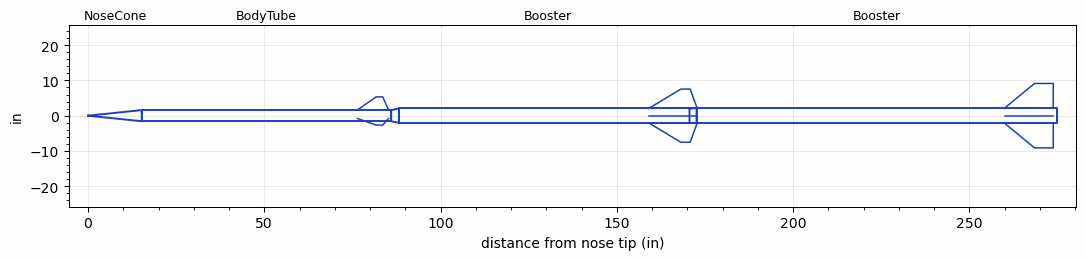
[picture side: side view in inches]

<RASAeroDocument>
 <FileVersion>2</FileVersion>
 <RocketDesign>
  <NoseCone>
   <Length>15.25</Length>
   <Diameter>3.17</Diameter>
   <Shape>Conical</Shape>
   <Location>0</Location>
  </NoseCone>
  <BodyTube>
   <Length>70.75</Length>
   <Diameter>3.17</Diameter>
   <Location>15.25</Location>
   <Fin>
    <Count>3</Count>
    <Chord>8.875</Chord>
    <Span>3.75</Span>
    <SweepDistance>5.3564</SweepDistance>
    <TipChord>1.875</TipChord>
    <Thickness>0.188</Thickness>
    <Location>9.625</Location>
    <AirfoilSection>Hexagonal</AirfoilSection>
    <FX1>0.75</FX1>
    <FX3>0.75</FX3>
   </Fin>
  </BodyTube>
  <Booster>
   <Length>84.625</Length>
   <Diameter>4.1</Diameter>
   <InsideDiameter>3.17</InsideDiameter>
   <Location>86</Location>
   <ShoulderLength>2.1875</ShoulderLength>
   <Fin>
    <Count>4</Count>
    <Chord>13.75</Chord>
    <Span>5.5</Span>
    <SweepDistance>9.125</SweepDistance>
    <TipChord>2.625</TipChord>
    <Thickness>0.23</Thickness>
    <Location>13.75</Location>
    <AirfoilSection>Hexagonal</AirfoilSection>
    <FX1>1</FX1>
    <FX3>1</FX3>
   </Fin>
  </Booster>
  <Booster>
   <Length>102.1875</Length>
   <Diameter>4.28</Diameter>
   <InsideDiameter>4.1</InsideDiameter>
   <LaunchShoeArea>0.233</LaunchShoeArea>
   <Location>170.625</Location>
   <ShoulderLength>2</ShoulderLength>
   <Fin>
    <Count>4</Count>
    <Chord>13.8125</Chord>
    <Span>7</Span>
    <SweepDistance>8.5</SweepDistance>
    <TipChord>5.3125</TipChord>
    <Thickness>0.32</Thickness>
    <Location>14.8125</Location>
    <AirfoilSection>Hexagonal Blunt Base</AirfoilSection>
    <FX1>1</FX1>
   </Fin>
  </Booster>
  <Surface>Smooth Paint</Surface>
  <ModifiedBarrowman>True</ModifiedBarrowman>
  <Turbulence>True</Turbulence>
  <UseBooster1>False</UseBooster1>
  <UseBooster2>False</UseBooster2>
 </RocketDesign>
 <LaunchSite>
  <Altitude>3750</Altitude>
  <Pressure>0</Pressure>
  <RodAngle>0</RodAngle>
  <RodLength>18</RodLength>
  <Temperature>80</Temperature>
  <WindSpeed>0</WindSpeed>
 </LaunchSite>
 <Recovery>
  <Altitude1>1000</Altitude1>
  <Altitude2>1000</Altitude2>
  <DeviceType1>None</DeviceType1>
  <DeviceType2>None</DeviceType2>
  <Event1>False</Event1>
  <Event2>False</Event2>
  <Size1>1</Size1>
  <Size2>1</Size2>
  <EventType1>None</EventType1>
  <EventType2>None</EventType2>
  <CD1>1.33</CD1>
  <CD2>1.33</CD2>
 </Recovery>
 <SimulationList>
  <Simulation>
   <SustainerEngine>M745WC  (GM)</SustainerEngine>
   <SustainerLaunchWt>21.6</SustainerLaunchWt>
   <SustainerNozzleDiameter>1</SustainerNozzleDiameter>
   <SustainerCG>56</SustainerCG>
   <SustainerIgnitionDelay>20.6</SustainerIgnitionDelay>
   <Booster1Engine>N2501-WH-P  (CTI)</Booster1Engine>
   <Booster1LaunchWt>67.63</Booster1LaunchWt>
   <Booster1SeparationDelay>0.9</Booster1SeparationDelay>
   <Booster1IgnitionDelay>6.5</Booster1IgnitionDelay>
   <Booster1CG>116</Booster1CG>
   <Booster1NozzleDiameter>1.75</Booster1NozzleDiameter>
   <IncludeBooster1>True</IncludeBooster1>
   <Booster2Engine>N5800-CS  (CTI)</Booster2Engine>
   <Booster2LaunchWt>122.8</Booster2LaunchWt>
   <Booster2Delay>0.9</Booster2Delay>
   <Booster2CG>177</Booster2CG>
   <Booster2NozzleDiameter>2.5</Booster2NozzleDiameter>
   <IncludeBooster2>True</IncludeBooster2>
   <TimetoApogee>121.5339</TimetoApogee>
   <MaxAltitude>155381.8</MaxAltitude>
   <MaxVelocity>2656.705</MaxVelocity>
  </Simulation>
  <Simulation>
   <SustainerEngine>M1401  (Ces)</SustainerEngine>
   <SustainerLaunchWt>23.6</SustainerLaunchWt>
   <SustainerNozzleDiameter>1</SustainerNozzleDiameter>
   <SustainerCG>60.2</SustainerCG>
   <SustainerIgnitionDelay>7.4</SustainerIgnitionDelay>
   <Booster1Engine>N1560-WH-MB-P  (CTI)</Booster1Engine>
   <Booster1LaunchWt>76.5</Booster1LaunchWt>
   <Booster1SeparationDelay>5</Booster1SeparationDelay>
   <Booster1IgnitionDelay>8.1</Booster1IgnitionDelay>
   <Booster1CG>118.6</Booster1CG>
   <Booster1NozzleDiameter>2.5</Booster1NozzleDiameter>
   <IncludeBooster1>True</IncludeBooster1>
   <Booster2Engine>N5800-CS  (CTI)</Booster2Engine>
   <Booster2LaunchWt>131.9</Booster2LaunchWt>
   <Booster2Delay>1</Booster2Delay>
   <Booster2CG>168.6</Booster2CG>
   <Booster2NozzleDiameter>2.5</Booster2NozzleDiameter>
   <IncludeBooster2>True</IncludeBooster2>
   <TimetoApogee>130.6739</TimetoApogee>
   <MaxAltitude>185017.8</MaxAltitude>
   <MaxVelocity>3202.877</MaxVelocity>
  </Simulation>
 </SimulationList>
</RASAeroDocument>
